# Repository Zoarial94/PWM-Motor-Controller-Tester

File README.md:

This is a board I designed and put together during my time as a mentor on the FRC team 4467 Titanium Titans. The original purpose of this device was to easily test Falcon 500 Motors since using the CAN interface made it sometimes difficult to troubleshoot. This board ties between a standard FRC battery, and a Falcon 500. A FRC valid circuit breaker is needed to complete the circuit. 

Version 1 of this board failed because I designed the board with one dc-to-dc converter, but ended up having to go with anther due to shortages. The footprint was mirrored on the new chip and it released the magic smoke after recieving 14V on the output side. This version's files are likely lost to time, but was used to make V2.

Version 2 (Currently uploaded) has a slightly smaller circuit board, but is essentially completely the same design. The programming header J2 was changed to the size it was supposed to be (V1 was too small), and U1 was flipped to match the parts I had on-hand. 

In the image below left to right: Version 2 PCB only. Version 1 PCB only. Version 2 with components except a ciruit breaker.

Unfortunately, I don't believe I ever recorded this working (Although it definitely has). I would have issues handing this to a student to use since everything is so exposed. Software and hardware wise, I think it is fine. (There should maybe be a protection circuit for the 5V side since U1 blew up in version 1 due to the previously mentioned design mistake.)

## Potential improvments. 
* Label the programming pins. (Needs to be reverse engineered again!)
* Use the virtical anderson connector for the battery connection. This allows for an off-the-shelf plastic sleeve to protect the exposed contacts. 
* Design a case. (This could be 3d printed, but with the forces needed to connect the battery, a 3d printed case will need to be designed to withstand large gripping forces.)
* Better protection on the 5V side.

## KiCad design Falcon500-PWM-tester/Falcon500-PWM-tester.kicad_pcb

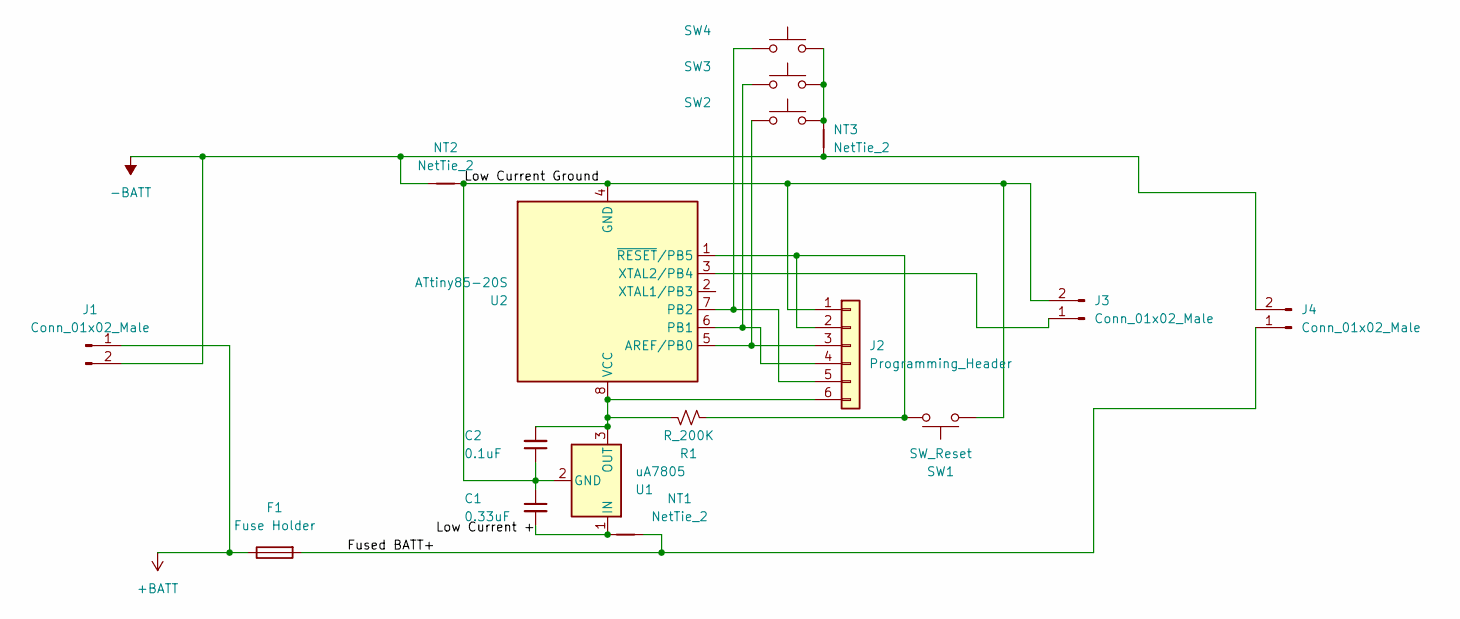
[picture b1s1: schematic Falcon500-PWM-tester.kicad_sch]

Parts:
C1: 0.33uF; C_0603_1608Metric_Pad1.08x0.95mm_HandSolder
C2: 0.1uF; C_0402_1005Metric_Pad0.74x0.62mm_HandSolder
F1: Fuse Holder; Fuseholder_Littelfuse_Style_ATO_Blade
J1: Conn_01x02_Male; MINI_HORIZONTAL_POWER_CLAW
J2: Programming_Header; PinHeader_1x06_P1.27mm_Vertical
J3: Conn_01x02_Male; TerminalBlock_Phoenix_MKDS-1,5-2-5.08_1x02_P5.08mm_Horizont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
J4: Conn_01x02_Male; PP44_2x1_Horizontal
NT1, NT2, NT3: NetTie_2; NetTie-2_SMD_Pad0.5mm
R1: R_200K; R_Axial_DIN0204_L3.6mm_D1.6mm_P7.62mm_Horizontal
SW1: SW_Reset; SW_PUSH_6mm
SW2: (no value)
SW3, SW4: SW_PUSH_6mm
U1: uA7805; SOT-89-3_Handsoldering
U2: ATtiny85-20S; SOIC-8W_5.3x5.3mm_P1.27mm

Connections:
+BATT: F1.1, J1.1
-BATT: J1.2, J4.2, NT2.1, NT3.1
/Fused BATT+: F1.2, J4.1, NT1.2
/Low Current +: C1.2, NT1.1, U1.1 (IN)
/Low Current Ground: C1.1, C2.1, J2.1, J3.2, NT2.2, SW1.2, U1.2 (GND), U2.4 (GND)
unnamed: C2.2, J2.6, R1.1, U1.3 (OUT), U2.8 (VCC)
unnamed: J2.2, R1.2, SW1.1, U2.1 (~RESET/PB5)
unnamed: J2.3, SW2.1, U2.5 (AREF/PB0)
unnamed: J2.4, SW3.1, U2.6 (PB1)
unnamed: J2.5, SW4.1, U2.7 (PB2)
unnamed: J3.1, U2.3 (XTAL2/PB4)
unnamed: NT3.2, SW2.2, SW3.2, SW4.2

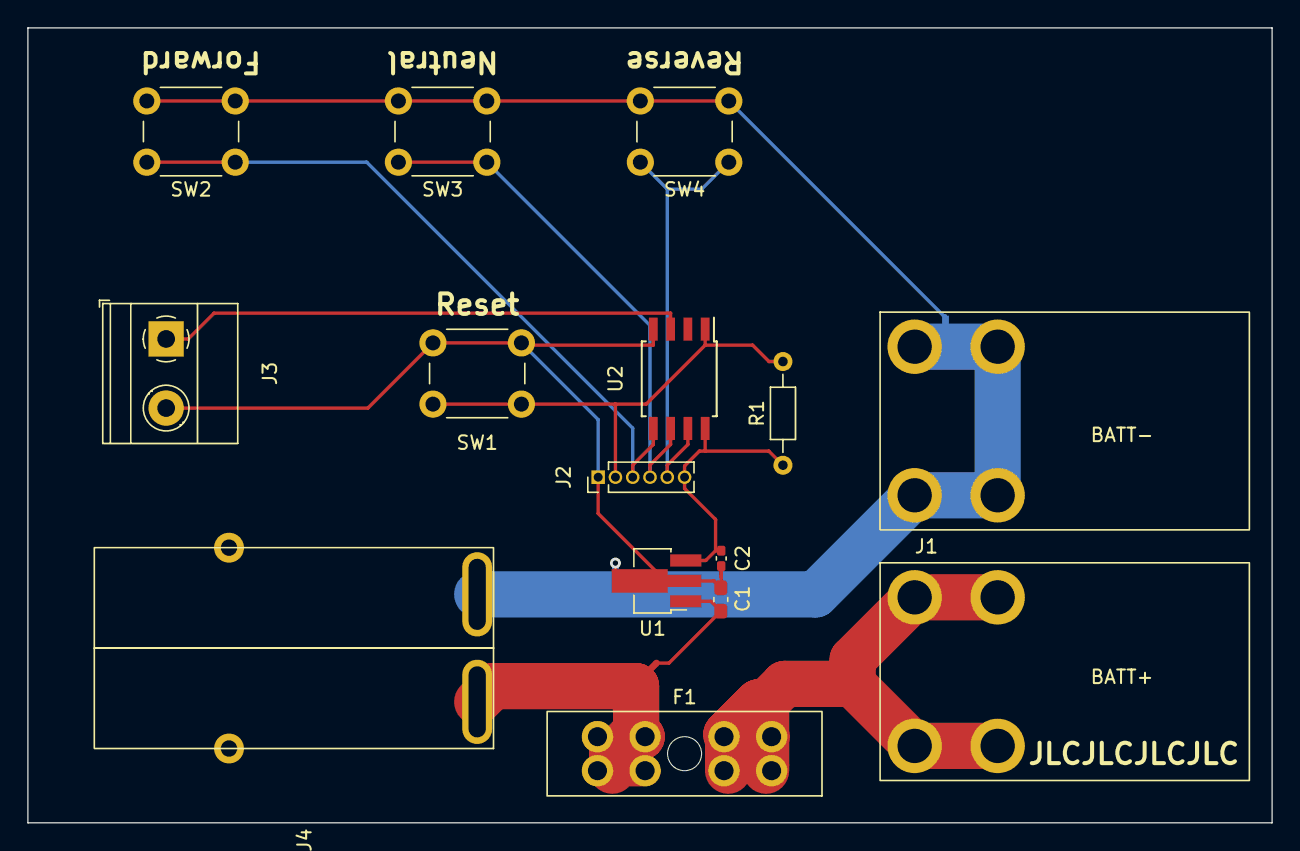
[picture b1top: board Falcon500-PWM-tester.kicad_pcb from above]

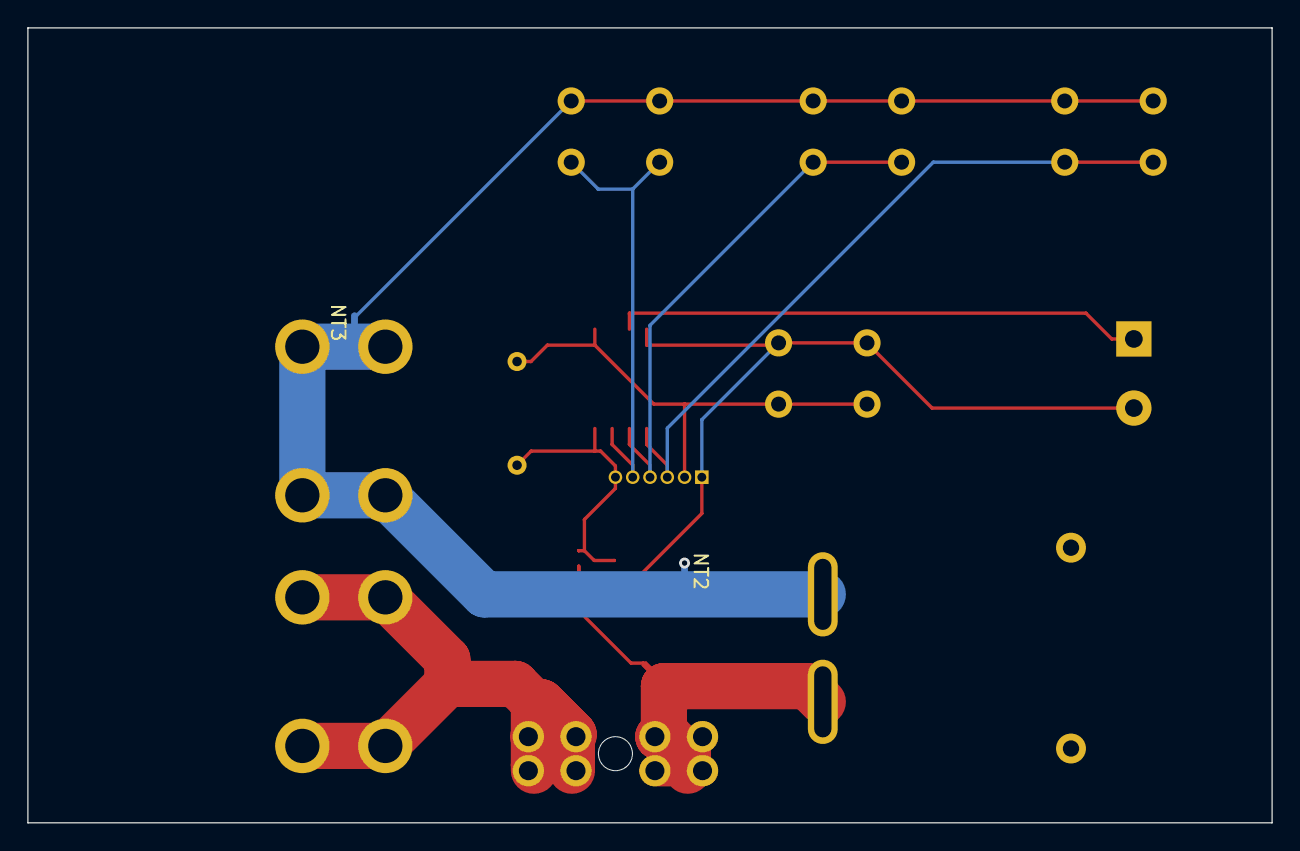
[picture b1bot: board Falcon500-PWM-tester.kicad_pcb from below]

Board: 2 copper layers, 91.4 x 58.4 mm, 17 parts (2 on the bottom side), 12 nets.

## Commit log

2024-07-14 Add ATtiny Code
2024-07-14 Upload circuit board files
